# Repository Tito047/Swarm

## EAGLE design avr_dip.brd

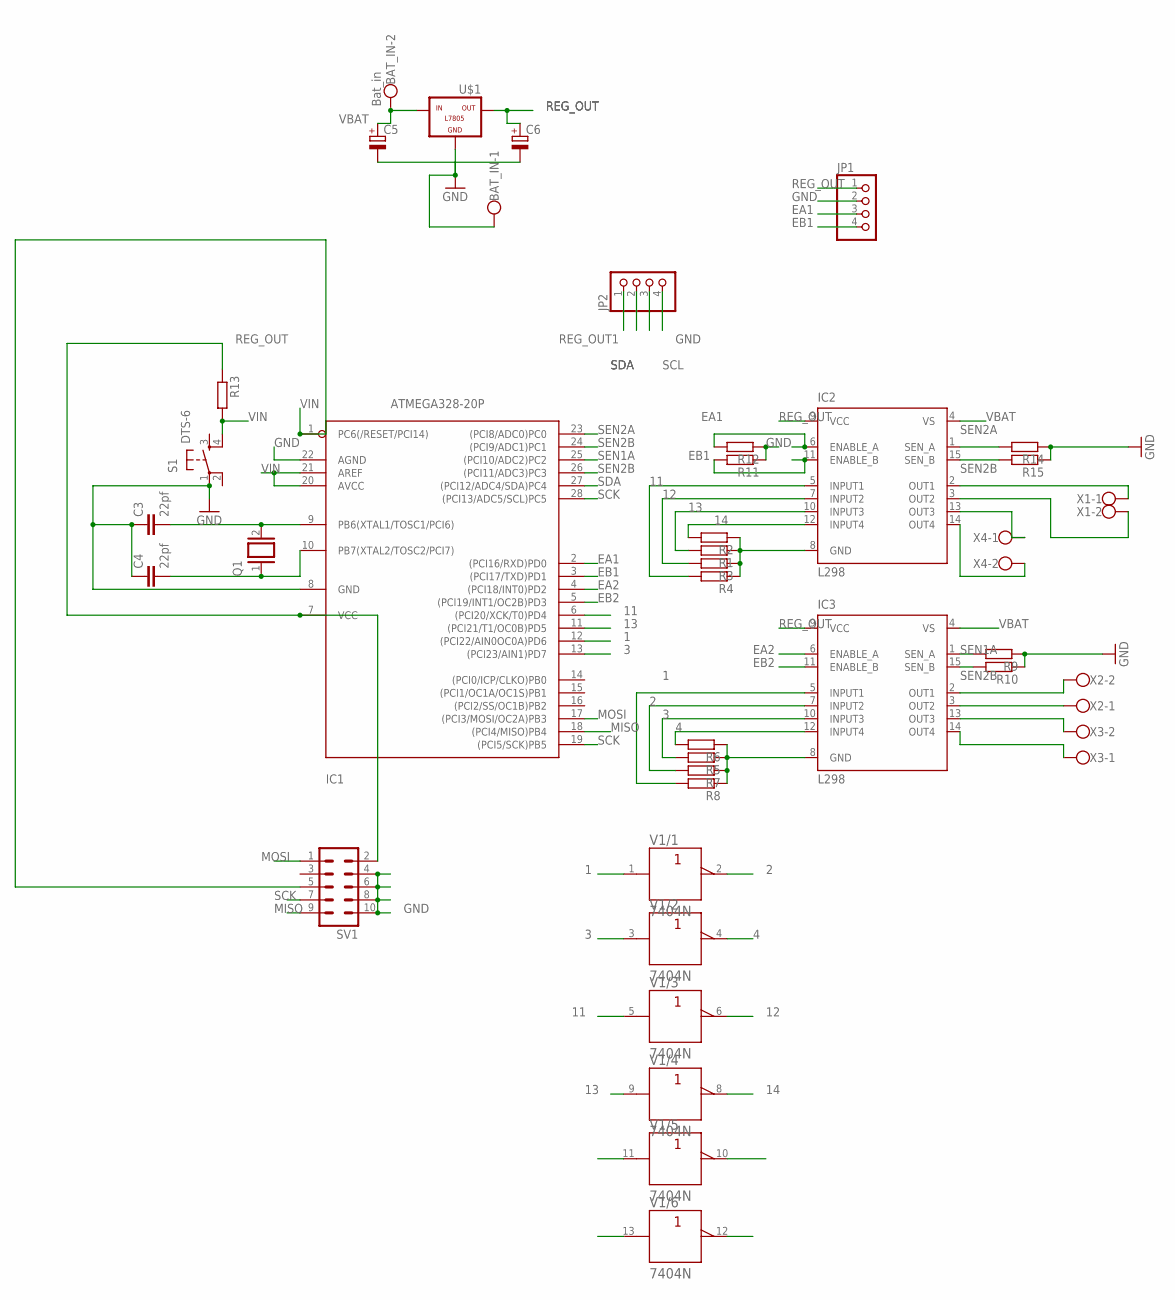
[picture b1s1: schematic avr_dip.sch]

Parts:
BAT_IN: Bat_in; W237-102
C3, C4: 22pf; C5B2.5
C5, C6: CPOL-EUE2-5; E2-5
IC1: ATMEGA328-20P; DIL28-3
IC2, IC3: L298; MULTIWATT-15
JP1, JP2: PINHD-1X4; 1X04
Q1: XTAL/S; QS
R1, R2, R3, R4, R5, R6, R7, R8, R9, R10, R11, R12, R13, R14, R15: R-EU_0207/10; 0207/10
S1: DTS-6
SV1: MA05-2
U$1: -L7805; L7805
V1: 7404N; DIL14
X1, X2, X3, X4: W237-102

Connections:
1: IC1.12 ((PCI22/AIN0OC0A)PD6), IC3.5 (INPUT1), R8.2, V1.1 (A)
2: IC3.7 (INPUT2), R7.2, V1.2 (Y)
3: IC1.13 ((PCI23/AIN1)PD7), IC3.10 (INPUT3), R5.2, V1.3 (A)
4: IC3.12 (INPUT4), R6.2, V1.4 (Y)
11: IC1.6 ((PCI20/XCK/T0)PD4), IC2.5 (INPUT1), R4.2, V1.5 (A)
12: IC2.7 (INPUT2), R3.2, V1.6 (Y)
13: IC1.11 ((PCI21/T1/OC0B)PD5), IC2.10 (INPUT3), R1.2, V1.9 (A)
14: IC2.12 (INPUT4), R2.2, V1.8 (Y)
+UB: V1.14 (+UB)
-UB: V1.7 (-UB)
EA1: IC1.2 ((PCI16/RXD)PD0), IC2.6 (ENABLE_A), JP1.3, R12.2
EA2: IC1.4 ((PCI18/INT0)PD2), IC3.6 (ENABLE_A)
EB1: IC1.3 ((PCI17/TXD)PD1), IC2.11 (ENABLE_B), JP1.4, R11.2
EB2: IC1.5 ((PCI19/INT1/OC2B)PD3), IC3.11 (ENABLE_B)
GND: BAT_IN.1, C3.1, C4.1, C5.-, C6.-, IC1.8 (GND), IC1.22 (AGND), JP1.2, JP2.4, R9.1, R10.1, R11.1, R12.1, R14.1, R15.1, S1.1, SV1.4, SV1.6, SV1.8, SV1.10, U$1.GND
MISO: IC1.18 ((PCI4/MISO)PB4), SV1.9
MOSI: IC1.17 ((PCI3/MOSI/OC2A)PB3), SV1.1
unnamed: IC2.13 (OUT3), X4.1
unnamed: C3.2, IC1.9 (PB6(XTAL1/TOSC1/PCI6)), Q1.2
unnamed: C4.2, IC1.10 (PB7(XTAL2/TOSC2/PCI7)), Q1.1
unnamed: IC2.8 (GND), R1.1, R2.1, R3.1, R4.1
unnamed: IC2.14 (OUT4), X4.2
unnamed: IC2.2 (OUT1), X1.1
unnamed: IC2.3 (OUT2), X1.2
unnamed: IC3.2 (OUT1), X2.2
unnamed: IC3.8 (GND), R5.1, R6.1, R7.1, R8.1
unnamed: IC3.3 (OUT2), X2.1
unnamed: IC3.13 (OUT3), X3.2
unnamed: IC3.14 (OUT4), X3.1
REG_OUT: C6.+, IC1.7 (VCC), IC2.9 (VCC), IC3.9 (VCC), JP1.1, R13.1, SV1.2, U$1.OUT
REG_OUT1: JP2.1
SCK: IC1.19 ((PCI5/SCK)PB5), IC1.28 ((PCI13/ADC5/SCL)PC5), SV1.7
SCL: JP2.3
SDA: IC1.27 ((PCI12/ADC4/SDA)PC4), JP2.2
SEN1A: IC1.25 ((PCI10/ADC2)PC2), IC3.1 (SEN_A), R9.2
SEN2A: IC1.23 ((PCI8/ADC0)PC0), IC2.1 (SEN_A), R14.2
SEN2B: IC1.24 ((PCI9/ADC1)PC1), IC1.26 ((PCI11/ADC3)PC3), IC2.15 (SEN_B), IC3.15 (SEN_B), R10.2, R15.2
VBAT: BAT_IN.2, C5.+, IC2.4 (VS), IC3.4 (VS), U$1.IN
VIN: IC1.1 (PC6(/RESET/PCI14)), IC1.20 (AVCC), IC1.21 (AREF), R13.2, S1.4, SV1.5

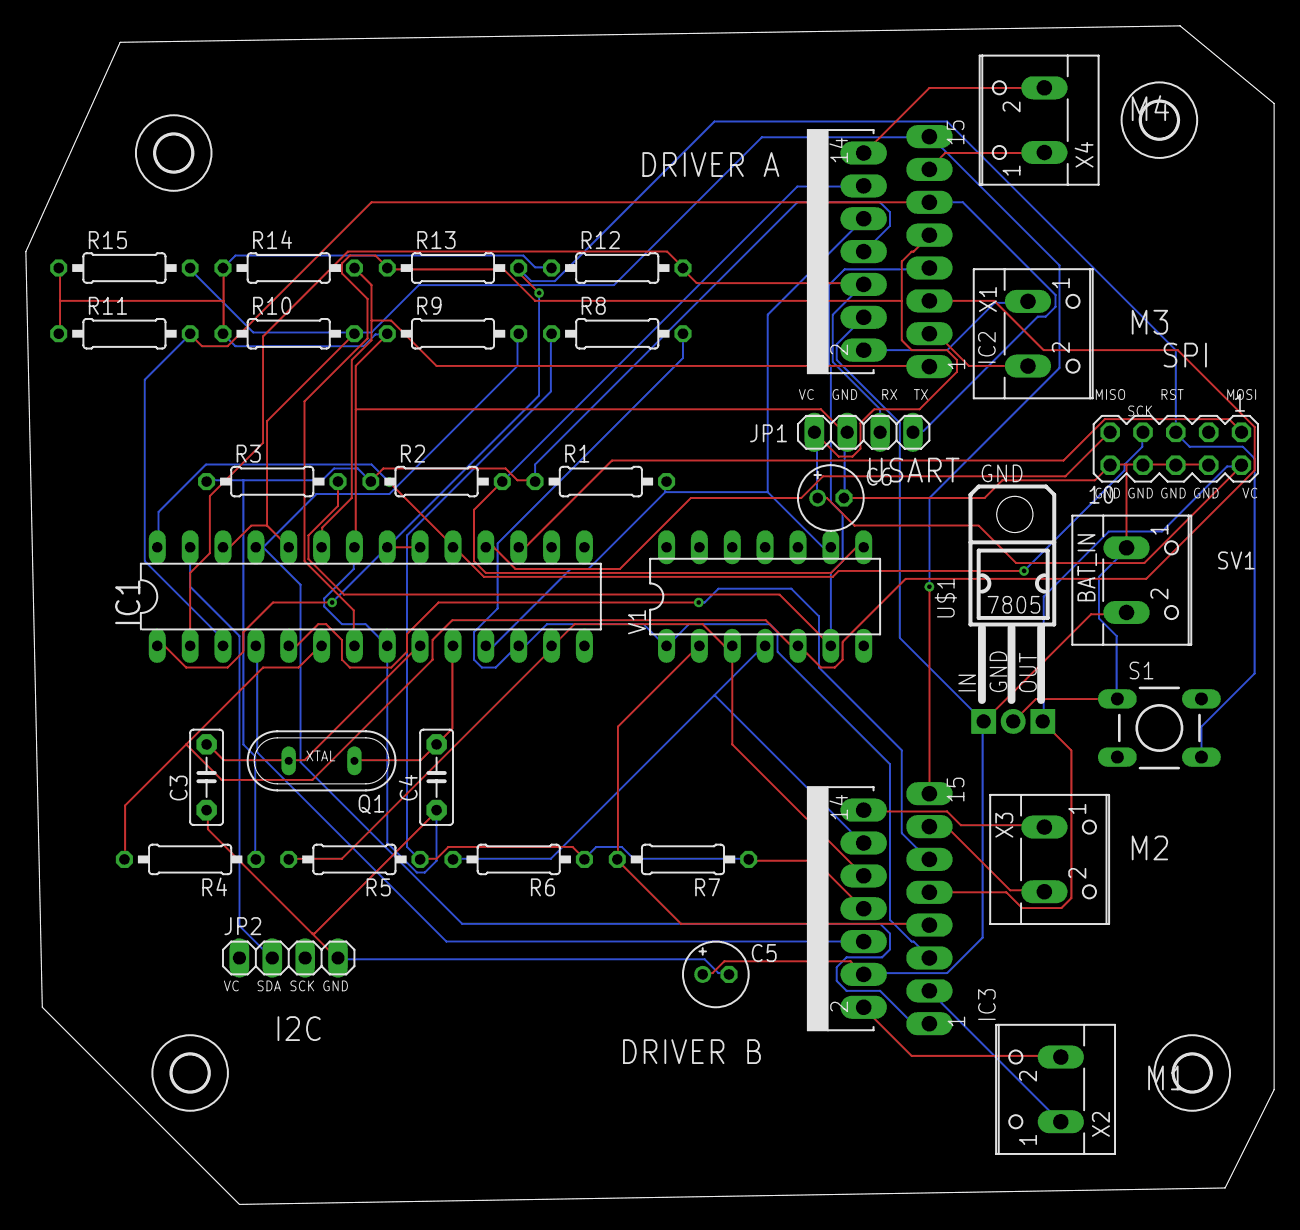
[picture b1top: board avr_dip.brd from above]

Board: 2 copper layers, 96.5 x 91.1 mm, 38 parts (0 on the bottom side), 35 nets.

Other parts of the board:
U$2, U$3, U$4, U$5: 2,8
